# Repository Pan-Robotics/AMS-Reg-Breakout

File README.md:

# AMS-Reg-Breakout
Breakout PCB for AMS1117 LDO Voltage Regulator

    • AMS1117 LDO Regulator: At the heart of our breakout board lies the AMS1117, a trusted and proven Low Dropout Voltage Regulator. 
    It provides a seamless transition from higher input voltages to a stable and precise output voltage, ensuring your circuits receive the power they need with minimal fluctuations.
    • Wide Voltage Range: Input voltage from 3.6 V to 18 V, Max Ouptut 12V with 1A max current draw.
    • Efficient and Reliable Design: Our breakout board is designed with efficiency and safety in mind, with a 1.2A fuse protecting your circuit elements from over current events, 
    and a heat sink to maximising heat dissipation which not only keeps your components safe from thermal spikes but also extends their operational lifespan.
    • Compact and Practical: We understand the value of space in your projects. Our breakout board features a compact design, making it a convenient choice for various applications where size matters.
    • Easy Integration: Don't waste time deciphering complicated setups. Our breakout board offers user-friendly connectivity with clearly labelled input and output pins. 
    You'll have your voltage regulation up and running quickly.
    • Enhanced Stability: The AMS1117 on our breakout board is known for its remarkable stability. It effectively filters out noise and provides a clean, 
    consistent voltage output – up to 120Hz input frequencies. Perfect for sensitive electronic circuits.

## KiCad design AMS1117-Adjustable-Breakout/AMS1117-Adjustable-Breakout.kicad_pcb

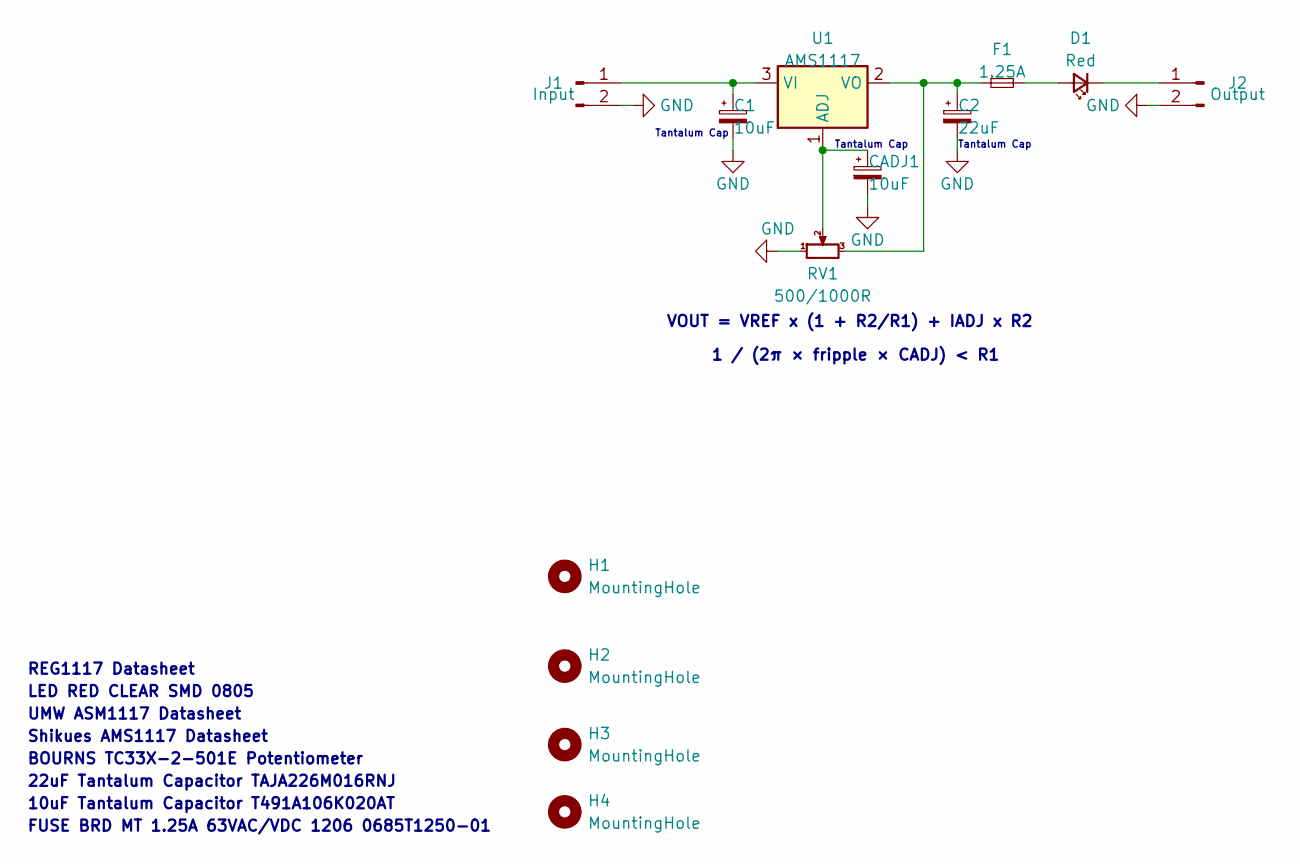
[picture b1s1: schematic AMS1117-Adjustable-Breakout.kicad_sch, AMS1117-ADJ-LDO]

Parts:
C1: 10uF; C_1206_3216Metric_Pad1.33x1.80mm_HandSolder
C2: 22uF; C_1206_3216Metric_Pad1.33x1.80mm_HandSolder
CADJ1: 10uF; C_1206_3216Metric_Pad1.33x1.80mm_HandSolder
D1: Red; LED_0805_2012Metric_Pad1.15x1.40mm_HandSolder
F1: 1.25A; Fuse_1206_3216Metric_Pad1.42x1.75mm_HandSolder
H1, H2, H3, H4: MountingHole; MountingHole_3.2mm_M3_DIN965_Pad
J1: Input; PinHeader_1x02_P2.54mm_Vertical
J2: Output; PinHeader_1x02_P2.54mm_Vertical
RV1: 500/1000R; Potentiometer_Bourns_TC33X_Vertical
U1: AMS1117; SOT-223-3_TabPin2

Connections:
GND: C1.2, C2.2, CADJ1.2, J1.2, J2.2, RV1.1
unnamed: D1.2 (A), F1.2
unnamed: D1.1 (K), J2.1
unnamed: C1.1, J1.1, U1.3 (VI)
unnamed: CADJ1.1, RV1.2, U1.1 (ADJ)
unnamed: C2.1, F1.1, RV1.3, U1.2 (VO)

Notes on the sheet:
REG1117 Datasheet
Tantalum Cap
10uF Tantalum Capacitor T491A106K020AT
UMW ASM1117 Datasheet
VOUT = VREF x (1 + R2/R1) + IADJ x R2
FUSE BRD MT 1.25A 63VAC/VDC 1206 0685T1250-01
Shikues AMS1117 Datasheet
22uF Tantalum Capacitor TAJA226M016RNJ
LED RED CLEAR SMD 0805
1 / (2π × fripple × CADJ) < R1
BOURNS TC33X-2-501E Potentiometer

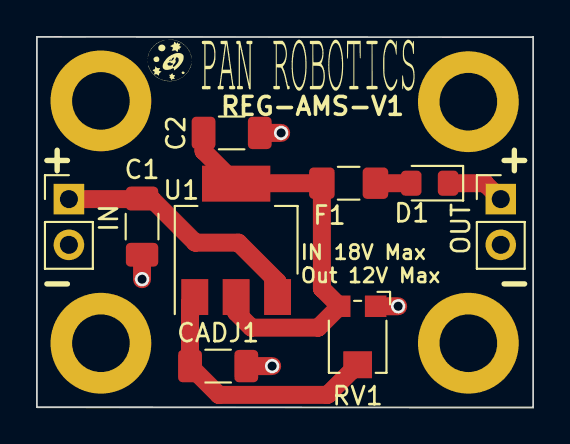
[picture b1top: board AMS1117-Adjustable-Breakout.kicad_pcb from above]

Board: 2 copper layers, 27.6 x 20.6 mm, 13 parts (0 on the bottom side), 6 nets.

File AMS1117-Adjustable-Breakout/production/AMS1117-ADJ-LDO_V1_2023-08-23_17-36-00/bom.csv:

Designator,Footprint,Quantity,Value,LCSC Part #
"C1, CADJ1",1206,2,10uF,
C2,1206,1,22uF,
D1,0805,1,Red,
F1,1206,1,1.25A,
"H1, H2, H3, H4",MountingHole_3.2mm_M3_DIN965_Pad,4,MountingHole,
J1,PinHeader_1x02_P2.54mm_Vertical,1,Input,
J2,PinHeader_1x02_P2.54mm_Vertical,1,Output,
RV1,Potentiometer_Bourns_TC33X_Vertical,1,500R,
U1,SOT-223-3_TabPin2,1,AMS1117,

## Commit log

2023-08-22 Initial Design Commit
    AD 22/08/23:
    Schematic and PCB V1
    Component Datasheet Links
2023-08-23 REG1117 Update
    AD 23/08/23:
    Datasheet for REG1117 Regulator added.
    1000R Trimmer option added to schematic.
2023-08-23 Pictures and 3D Model
2023-08-27 Product Description Added
    AD 27/08/23:
    Added Docx and PDF of Product description.
    Rearranged file Structure.
2023-09-03 Board Length Reduced
    AD 03/09/23
2024-01-16 Clerical Updates
